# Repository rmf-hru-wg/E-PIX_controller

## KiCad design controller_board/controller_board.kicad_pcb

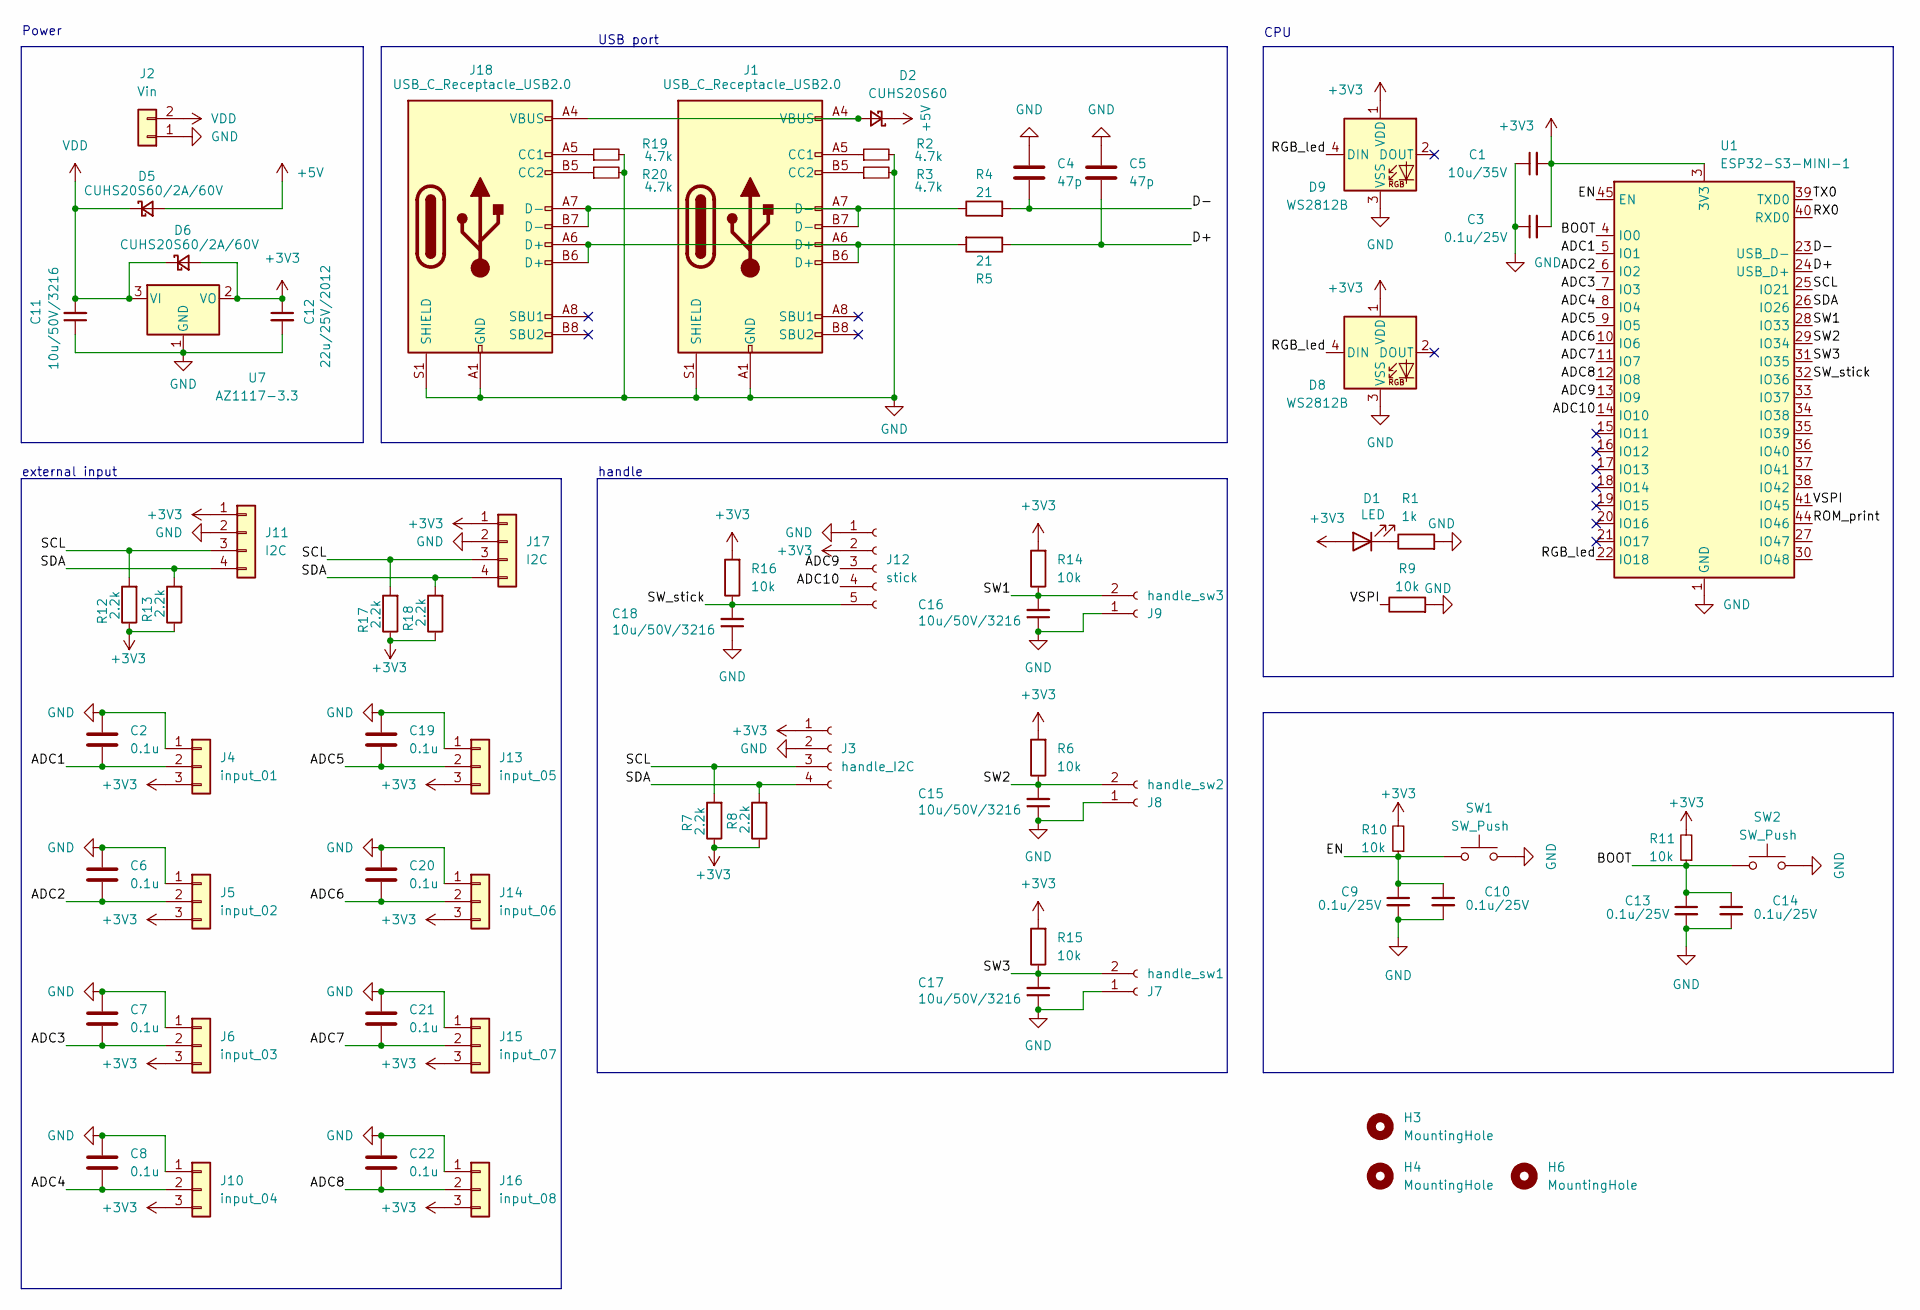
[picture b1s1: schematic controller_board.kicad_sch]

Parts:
C1: 10u/35V; C_1206_3216Metric
C2, C6, C7, C8, C19, C20, C21, C22: 0.1u; C_0603_1608Metric
C3, C9, C10, C13, C14: 0.1u/25V; C_0603_1608Metric
C4, C5: 47p; C_0201_0603Metric
C11, C15, C16, C17, C18: 10u/50V/3216; C_1206_3216Metric
C12: 22u/25V/2012; C_0805_2012Metric
D1: LED; LED_0603_1608Metric
D2: CUHS20S60; Diode_US2H
D5, D6: CUHS20S60/2A/60V; Diode_US2H
D8, D9: WS2812B; LED_WS2812B_PLCC4_5.0x5.0mm_P3.2mm
H3, H4, H6: MountingHole; MountingHole_3.2mm_M3_DIN965
J1, J18: USB_C_Receptacle_USB2.0; USB_C_Receptacle_XKB_U262-16XN-4BVC11_with_model
J2: Vin; PinSocket_1x02_P2.54mm_Vertical
J3: handle_I2C; PinSocket_1x04_P2.54mm_Vertical
J4: input_01; JST_XH_B3B-XH-A_1x03_P2.50mm_Vertical
J5: input_02; JST_XH_B3B-XH-A_1x03_P2.50mm_Vertical
J6: input_03; JST_XH_B3B-XH-A_1x03_P2.50mm_Vertical
J7: handle_sw1; PinSocket_1x02_P2.54mm_Vertical
J8: handle_sw2; PinSocket_1x02_P2.54mm_Vertical
J9: handle_sw3; PinSocket_1x02_P2.54mm_Vertical
J10: input_04; JST_XH_B3B-XH-A_1x03_P2.50mm_Vertical
J11, J17: I2C; JST_XH_B4B-XH-A_1x04_P2.50mm_Vertical
J12: stick; PinSocket_1x05_P2.54mm_Vertical
J13: input_05; JST_XH_B3B-XH-A_1x03_P2.50mm_Vertical
J14: input_06; JST_XH_B3B-XH-A_1x03_P2.50mm_Vertical
J15: input_07; JST_XH_B3B-XH-A_1x03_P2.50mm_Vertical
J16: input_08; JST_XH_B3B-XH-A_1x03_P2.50mm_Vertical
R1: 1k; R_0805_2012Metric
R2, R3, R19, R20: 4.7k; R_0805_2012Metric
R4, R5: 21; R_0603_1608Metric
R6, R9, R10, R11, R14, R15, R16: 10k; R_0603_1608Metric
R7, R8, R12, R13, R17, R18: 2.2k; R_0805_2012Metric
SW1, SW2: SW_Push; SW_SKRPACE010
U1: ESP32-S3-MINI-1; ESP32-S2-MINI-1
U7: AZ1117-3.3; SOT-223-3_TabPin2

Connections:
+3V3: C1.2, C3.2, C12.1, D1.2 (A), D6.2 (A), D8.1 (VDD), D9.1 (VDD), J3.1, J4.3, J5.3, J6.3, J10.3, J11.1, J12.2, J13.3, J14.3, J15.3, J16.3, J17.1, R6.2, R7.1, R8.1, R10.2, R11.2, R12.1, R13.1, R14.2, R15.2, R16.2, R17.1, R18.1, U1.3 (3V3), U7.2 (VO)
+5V: D2.1 (K), D5.2 (A)
/ADC1: C2.2, J4.2, U1.5 (IO1)
/ADC2: C6.2, J5.2, U1.6 (IO2)
/ADC3: C7.2, J6.2, U1.7 (IO3)
/ADC4: C8.2, J10.2, U1.8 (IO4)
/ADC5: C19.2, J13.2, U1.9 (IO5)
/ADC6: C20.2, J14.2, U1.10 (IO6)
/ADC7: C21.2, J15.2, U1.11 (IO7)
/ADC8: C22.2, J16.2, U1.12 (IO8)
/ADC9: J12.3, U1.13 (IO9)
/ADC10: J12.4, U1.14 (IO10)
/BOOT: C13.1, C14.1, R11.1, SW2.1, U1.4 (IO0)
/D+: C5.2, R5.1, U1.24 (USB_D+)
/D-: C4.2, R4.2, U1.23 (USB_D-)
/EN: C9.1, C10.1, R10.1, SW1.1, U1.45 (EN)
/RGB_led: D8.4 (DIN), D9.4 (DIN), U1.22 (IO18)
/ROM_print: U1.44 (IO46)
/RX0: U1.40 (RXD0)
/SCL: J3.3, J11.3, J17.3, R7.2, R12.2, R17.2, U1.25 (IO21)
/SDA: J3.4, J11.4, J17.4, R8.2, R13.2, R18.2, U1.26 (IO26)
/SW1: C16.2, J9.2, R14.1, U1.28 (IO33)
/SW2: C15.2, J8.2, R6.1, U1.29 (IO34)
/SW3: C17.2, J7.2, R15.1, U1.31 (IO35)
/SW_stick: C18.2, J12.5, R16.1, U1.32 (IO36)
/TX0: U1.39 (TXD0)
/VSPI: R9.1, U1.41 (IO45)
GND: C1.1, C2.1, C3.1, C4.1, C5.1, C6.1, C7.1, C8.1, C9.2, C10.2, C11.1, C12.2, C13.2, C14.2, C15.1, C16.1, C17.1, C18.1, C19.1, C20.1, C21.1, C22.1, D8.3 (VSS), D9.3 (VSS), J1.A1 (GND), J1.A12 (GND), J1.B1 (GND), J1.B12 (GND), J1.S1 (SHIELD), J2.1, J3.2, J4.1, J5.1, J6.1, J7.1, J8.1, J9.1, J10.1, J11.2, J12.1, J13.1, J14.1, J15.1, J16.1, J17.2, J18.A1 (GND), J18.A12 (GND), J18.B1 (GND), J18.B12 (GND), J18.S1 (SHIELD), R1.2, R2.2, R3.2, R9.2, R19.2, R20.2, SW1.2, SW2.2, U1.1 (GND), U1.2 (GND), U1.42 (GND), U1.43 (GND), U1.46 (GND), U1.47 (GND), U1.48 (GND), U1.49 (GND), U1.50 (GND), U1.51 (GND), U1.52 (GND), U1.53 (GND), U1.54 (GND), U1.55 (GND), U1.56 (GND), U1.57 (GND), U1.58 (GND), U1.59 (GND), U1.60 (GND), U1.61 (GND), U1.62 (GND), U1.63 (GND), U1.64 (GND), U1.65 (GND), U7.1 (GND)
unnamed: D1.1 (K), R1.1
unnamed: D2.2 (A), J1.A4 (VBUS), J1.A9 (VBUS), J1.B4 (VBUS), J1.B9 (VBUS), J18.A4 (VBUS), J18.A9 (VBUS), J18.B4 (VBUS), J18.B9 (VBUS)
unnamed: J1.A5 (CC1), R2.1
unnamed: J1.B5 (CC2), R3.1
unnamed: J1.A6 (D+), J1.B6 (D+), J18.A6 (D+), J18.B6 (D+), R5.2
unnamed: J1.A7 (D-), J1.B7 (D-), J18.A7 (D-), J18.B7 (D-), R4.1
unnamed: J18.A5 (CC1), R19.1
unnamed: J18.B5 (CC2), R20.1
VDD: C11.2, D5.1 (K), D6.1 (K), J2.2, U7.3 (VI)

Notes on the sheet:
CPU
external input
USB port
Power
handle

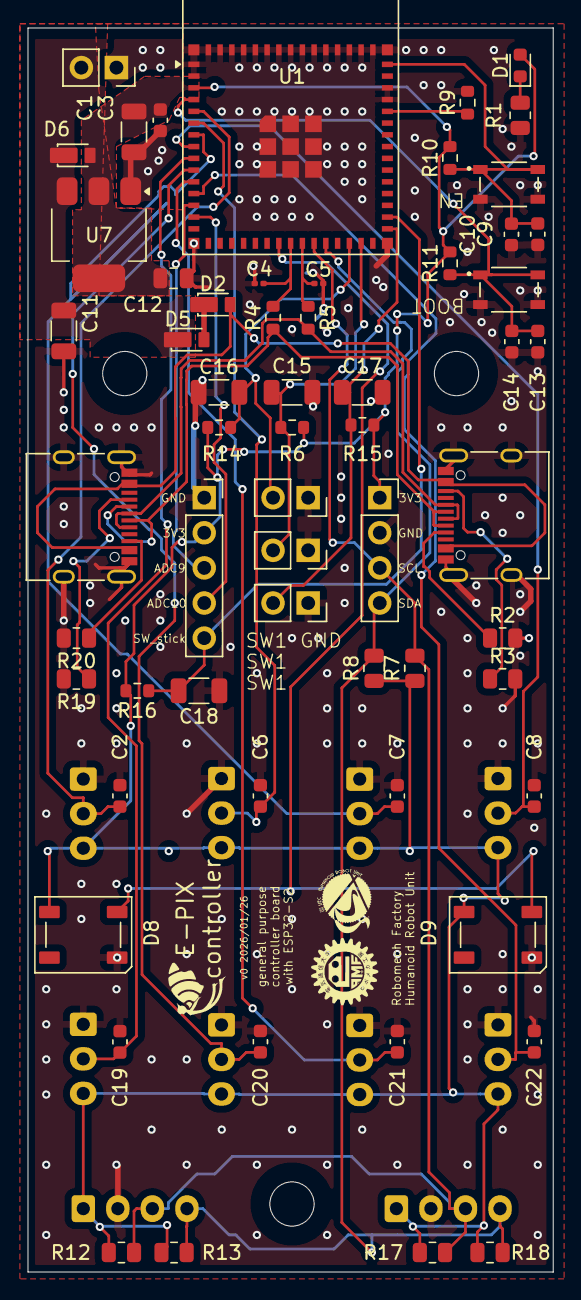
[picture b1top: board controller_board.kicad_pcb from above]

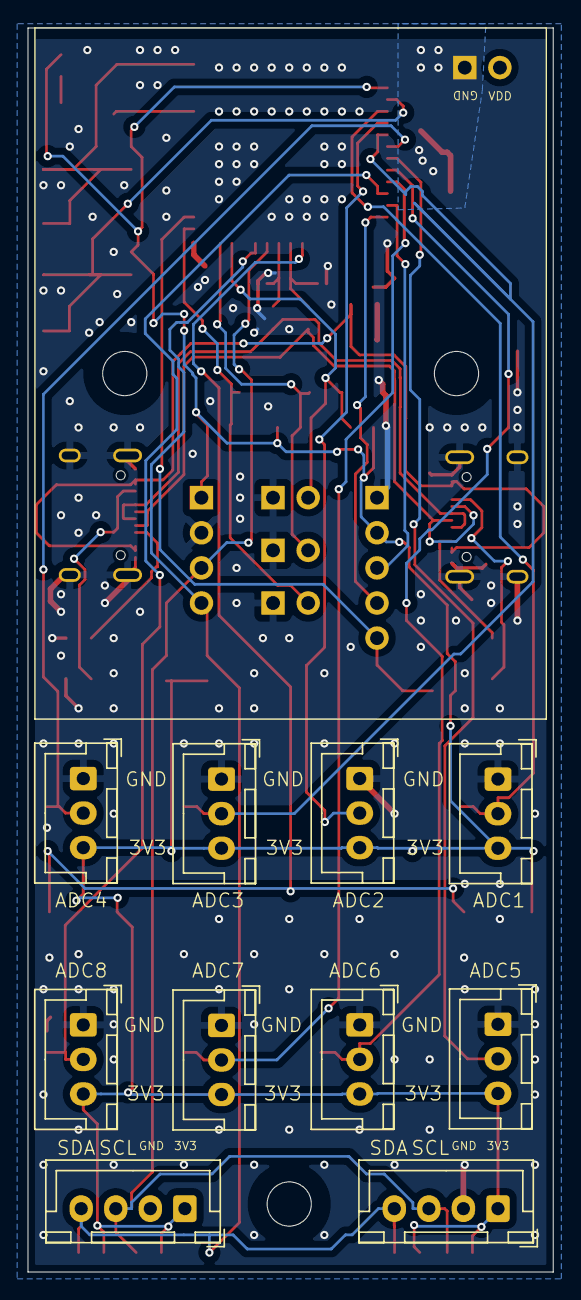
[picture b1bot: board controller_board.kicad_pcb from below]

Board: 2 copper layers, 38.0 x 90.0 mm, 73 parts (12 on the bottom side), 34 nets.

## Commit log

2026-01-22 first commit. create most of the hard of controller
2026-01-25 free routing
2026-02-01 ordered controller. create body controller model
2026-02-02 shape mistaken
2026-02-02 create new body
2026-02-03 making monitor cover and board surroundings
2026-02-05 create buckle arounds
2026-02-09 move main codes
2026-02-10 create ConteollerVolume and most of the main code. waiting for test
2026-02-10 update mapping method
2026-02-11 correct mapping method
2026-02-11 set all the initial positions
2026-02-11 update elbow
2026-02-16 change init position
2026-02-21 enable to display received msg
2026-02-23 simplified display functions
